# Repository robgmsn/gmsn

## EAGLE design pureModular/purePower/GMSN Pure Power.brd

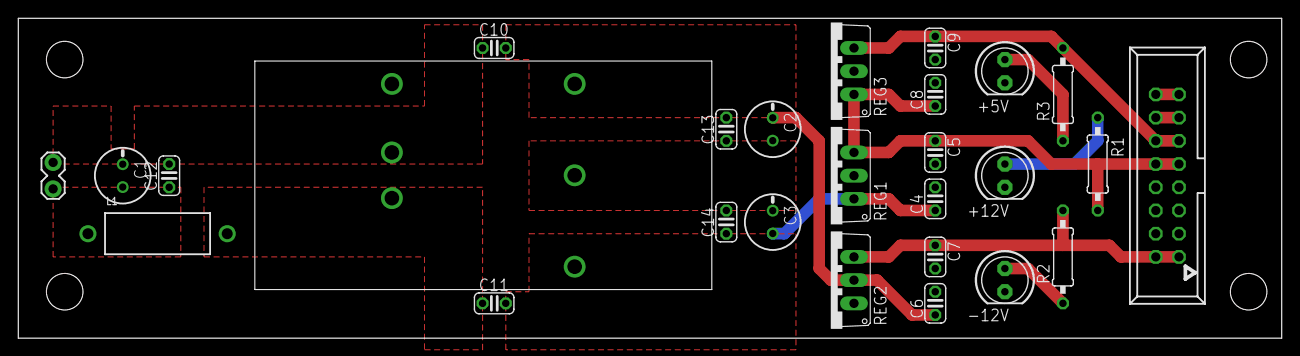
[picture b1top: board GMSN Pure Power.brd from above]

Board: 2 copper layers, 138.2 x 35.0 mm, 27 parts (0 on the bottom side), 13 nets.

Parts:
+5V, +12V: LED5MM
-12V: LED5MM
C1, C2, C3: SANYO-OSCON_D
C4, C5, C6, C7, C8, C9, C10, C11, C12, C13, C14: C025-024X044
JP1: M02LOCK; 1X02_LOCK
L1: AXIAL-0.6
R1, R2, R3: 0207/10
REG1, REG3: V-REGTO220V; TO220V
REG2: V-REG-NEGTO220V; TO220V
U$1: URA241XLD-20WR3
U$11: EURO_POWER_16; POWER_SHROUDED

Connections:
+5V: C9.1, R3.2, REG3.3, U$11.+5, U$11.+5A
+12V: C5.1, C8.1, R1.2, REG1.3, REG3.1, U$11.+12, U$11.+12A
+15V: C3.+, C4.1, C11.2, C14.1, REG1.1, U$1.P$3
-12V: C7.1, R2.2, REG2.3, U$11.-12, U$11.-12A
-15V: C2.-, C6.1, C10.2, C13.2, REG2.2, U$1.P$5
GND: +5V.K, +12V.K, -12V.K, C1.-, C2.+, C3.-, C4.2, C5.2, C6.2, C7.2, C8.2, C9.2, C10.1, C12.2, C13.1, C14.2, JP1.2, REG1.2, REG2.1, REG3.2, U$1.P$1, U$1.P$4, U$11.3G, U$11.4G, U$11.5G, U$11.6G, U$11.7G, U$11.8G
unnamed: U$11.GATE, U$11.GATEA
unnamed: U$11.CV, U$11.CVA
unnamed: C11.1, L1.P$2, U$1.P$2
unnamed: +12V.A, R1.1
unnamed: -12V.A, R2.1
unnamed: +5V.A, R3.1
unnamed: C1.+, C12.1, JP1.1, L1.P$1

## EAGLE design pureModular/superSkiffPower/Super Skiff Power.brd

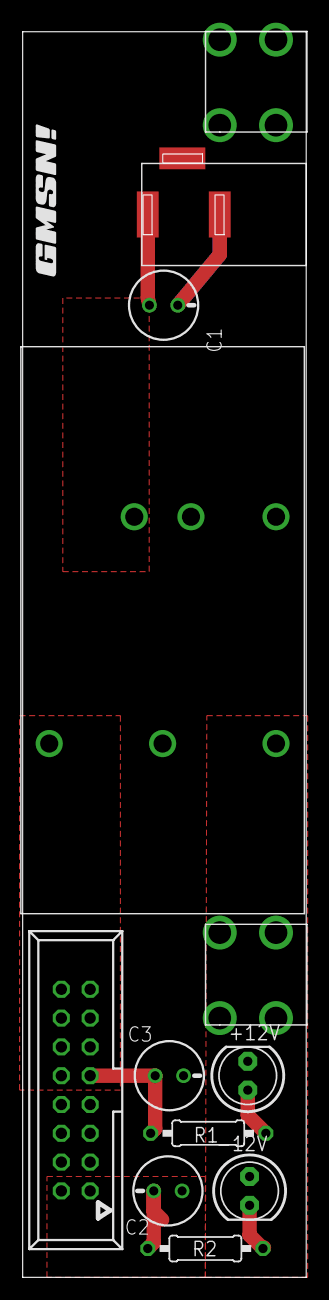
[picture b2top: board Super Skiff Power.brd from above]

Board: 2 copper layers, 25.0 x 109.8 mm, 14 parts (1 on the bottom side), 6 nets.

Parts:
+12V: LED5MM
-12V: LED5MM
C1, C2, C3: 100uF; SANYO-OSCON_D
R1, R2: 47k; 0207/10
U$1: URA241XLD-20WR3
U$2: DC-POWER
U$3: EURO_POWER_16; POWER_SHROUDED
U$4, U$5: GMSN!_LOGO
U$6, U$8: PCB-2-MOUNTING

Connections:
+12V: C3.+, R1.2, U$1.P$3, U$3.+12, U$3.+12A
-12V: C2.-, R2.2, U$1.P$5, U$3.-12, U$3.-12A
GND: +12V.K, -12V.A, C1.-, C2.+, C3.-, U$1.P$1, U$1.P$4, U$2.SLEEVEBOT, U$2.SLEEVETOP, U$3.3G, U$3.4G, U$3.5G, U$3.6G, U$3.7G, U$3.8G, U$6.P$1, U$6.P$2, U$6.P$3, U$6.P$4, U$8.P$1, U$8.P$2, U$8.P$3, U$8.P$4
unnamed: C1.+, U$1.P$2, U$2.PINBOT, U$2.PINTOP
unnamed: +12V.A, R1.1
unnamed: -12V.K, R2.1
